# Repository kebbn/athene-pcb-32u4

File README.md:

# athene-pcb-32u4
 65% PCB design for the Athene keyboard by KL using the ATmega32u4 MCU.
 
 This project has been deprecated and is no longer supported. The more current design and variant is built off of the STM32F072 MCU, within the athene-pcb-f072 project.

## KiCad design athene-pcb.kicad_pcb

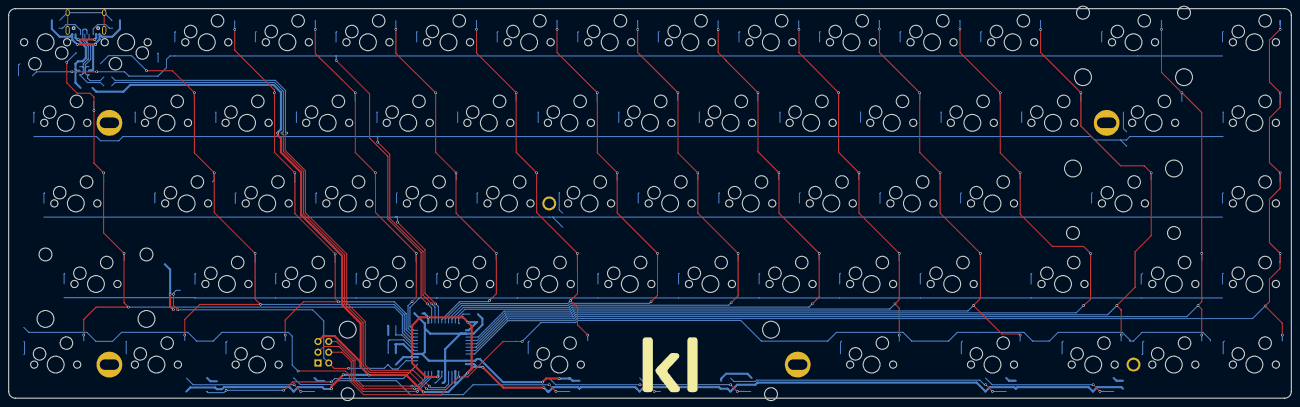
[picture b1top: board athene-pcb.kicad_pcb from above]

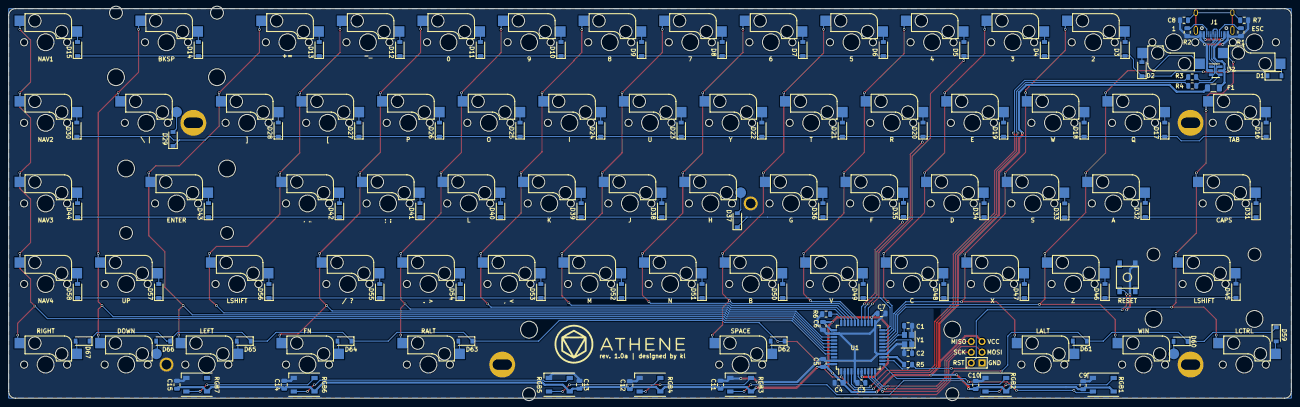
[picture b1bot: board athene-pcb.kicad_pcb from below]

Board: 2 copper layers, 303.2 x 92.1 mm, 182 parts (172 on the bottom side), 112 nets.

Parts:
C1, C2: 22pF; C_0805_2012Metric
C3: 1uF; C_0805_2012Metric
C4, C5, C6, C9, C10, C11, C12, C13, C14, C15: 0.1uF; C_0805_2012Metric
C7: 10uF; C_0805_2012Metric
C8: 4.7nF; C_0805_2012Metric
D1, D2, D3, D4, D5, D6, D7, D8, D9, D10, D11, D12, D13, D14, D15, D16, D17, D18, D19, D20, D21, D22, D23, D24, D25, D26, D27, D28, D29, D30, D31, D32, D33, D34, D35, D36, D37, D38, D39, D40, D41, D42, D43, D44, D45, D46, D47, D48, D49, D50, D51, D52, D53, D54, D55, D56, D57, D58, D59, D60, D61, D62, D63, D64, D65, D66, D67: D; D_SOD-123
F1: 500mA; Fuse_1206_3216Metric
HOLE5, HOLE5#2: MountingHole_4mm; MountingHole_M2
J1: HRO-TYPE-C-31-M-12
J2: AVR-ISP-6; Reset_Pretty-Mask
K1, K2, K3, K4, K5, K6, K7, K8, K9, K10, K11, K12, K13, K14, K15, K16, K17, K18, K19, K20, K21, K22, K23, K24, K25, K26, K27, K28, K30, K31, K32, K33, K34, K35, K36, K38, K39, K40, K41, K42, K43, K44, K45, K46, K47, K48, K49, K50, K51, K52, K53, K54, K55, K56, K57, K58, K59, K61, K62, K63, K64, K65, K67: KEYSW; Kailh_MX_Socket (3D)
K29, K37, K60, K66: KEYSW; Kailh_MX_Socket (3D) 1_Circle
Poker_oval_hole: VAL**; Poker_oval_hole
Poker_oval_hole#2, Poker_oval_hole#3, Poker_oval_hole#4: VAL**; Poker_oval_hole
R1, R2: 5.1k; R_0805_2012Metric
R3, R4: 22; R_0805_2012Metric
R5, R6: 10k; R_0805_2012Metric
R7: 1M; R_0805_2012Metric
RGB1, RGB2, RGB3, RGB4, RGB5, RGB6, RGB7: SK6812; LED_SK6812_PLCC4_5.0x5.0mm_P3.2mm
S1: SW_Push; SKQG-1155865
ST_BKSP: Stabilizer; Mx_Stab_200
ST_ENTER: Stabilizer; Mx_Stab_225
ST_LSHIFT: Stabilizer; Mx_Stab_200
ST_SPACE: Stabilizer; Mx_Stab_625
U1: ATmega32U4-AU; TQFP-44_10x10mm_P0.8mm
U2: SRV05-4-P-T7; SOT-23-6
Y1: XTAL; Crystal_SMD_3225-4Pin_3.2x2.5mm
athene logo: LOGO; athene
kl logo: LOGO; kl

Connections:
COL0: K1.1, K16.2, K31.2, K45.2, K59.2, U1.18 (PD0)
COL1: K2.2, K17.2, K32.2, K46.2, K60.2, U1.19 (PD1)
COL2: K3.2, K18.2, K33.2, K47.2, K61.2, U1.20 (PD2)
COL3: K4.2, K19.2, K34.2, K48.2, U1.21 (PD3)
COL4: K5.2, K20.2, K35.2, K49.2, U1.28 (PB4)
COL5: K6.2, K21.2, K36.2, K50.2, K62.2, U1.29 (PB5)
COL6: K7.2, K22.2, K37.2, K51.2, U1.30 (PB6)
COL7: K8.2, K23.2, K38.2, K52.2, U1.31 (PC6)
COL8: K9.2, K24.2, K39.2, K53.2, U1.32 (PC7)
COL9: K10.2, K25.2, K40.2, K54.2, K63.2, U1.36 (PF7)
COL10: K11.2, K26.2, K41.2, K55.2, K64.2, U1.37 (PF6)
COL11: K12.2, K27.2, K42.2, K56.2, U1.38 (PF5)
COL12: K13.2, K28.2, K43.2, K65.2, U1.39 (PF4)
COL13: K14.2, K29.2, K57.2, K66.2, U1.40 (PF1)
COL14: K15.2, K30.2, K44.2, K58.2, K67.2, U1.41 (PF0)
D+: R3.2, U1.4 (D+)
D-: R4.2, U1.3 (D-)
DBUS+: J1.6 (DP1), J1.8 (DP2), R3.1, U2.1 (IO1), U2.3 (IO2)
DBUS-: J1.5 (DN2), J1.7 (DN1), R4.1, U2.4 (IO3), U2.6 (IO4)
GND: C1.1, C2.1, C3.1, C4.2, C5.2, C6.2, C7.2, C8.2, C9.2, C10.2, C11.2, C12.2, C13.2, C14.2, C15.2, J1.1 (GND), J1.12 (GND), J2.6 (GND), R1.2, R2.2, R6.1, R7.1, RGB1.1 (VSS), RGB2.1 (VSS), RGB3.1 (VSS), RGB4.1 (VSS), RGB5.1 (VSS), RGB6.1 (VSS), RGB7.1 (VSS), S1.1, U1.5 (UGND), U1.15 (GND), U1.23 (GND), U1.35 (GND), U1.43 (GND), U2.2 (VN), Y1.2, Y1.4
MISO: J2.1 (MISO), U1.11 (PB3)
MOSI: J2.4 (MOSI), U1.10 (PB2)
unnamed: C1.2, U1.17 (XTAL1), Y1.3
unnamed: C2.2, U1.16 (XTAL2), Y1.1
unnamed: C3.2, U1.6 (UCAP)
unnamed: C8.1, J1.13 (SHIELD), R7.2
unnamed: D1.2 (A), K1.2
unnamed: D2.2 (A), K2.1
unnamed: D3.2 (A), K3.1
unnamed: D4.2 (A), K4.1
unnamed: D5.2 (A), K5.1
unnamed: D6.2 (A), K6.1
unnamed: D7.2 (A), K7.1
unnamed: D8.2 (A), K8.1
unnamed: D9.2 (A), K9.1
unnamed: D10.2 (A), K10.1
unnamed: D11.2 (A), K11.1
unnamed: D12.2 (A), K12.1
unnamed: D13.2 (A), K13.1
unnamed: D14.2 (A), K14.1
unnamed: D15.2 (A), K15.1
unnamed: D16.2 (A), K16.1
unnamed: D17.2 (A), K17.1
unnamed: D18.2 (A), K18.1
unnamed: D19.2 (A), K19.1
unnamed: D20.2 (A), K20.1
unnamed: D21.2 (A), K21.1
unnamed: D22.2 (A), K22.1
unnamed: D23.2 (A), K23.1
unnamed: D24.2 (A), K24.1
unnamed: D25.2 (A), K25.1
unnamed: D26.2 (A), K26.1
unnamed: D27.2 (A), K27.1
unnamed: D28.2 (A), K28.1
unnamed: D29.2 (A), K29.1
unnamed: D30.2 (A), K30.1
unnamed: D31.2 (A), K31.1
unnamed: D32.2 (A), K32.1
unnamed: D33.2 (A), K33.1
unnamed: D34.2 (A), K34.1
unnamed: D35.2 (A), K35.1
unnamed: D36.2 (A), K36.1
unnamed: D37.2 (A), K37.1
unnamed: D38.2 (A), K38.1
unnamed: D39.2 (A), K39.1
unnamed: D40.2 (A), K40.1
unnamed: D41.2 (A), K41.1
unnamed: D42.2 (A), K42.1
unnamed: D43.2 (A), K43.1
unnamed: D44.2 (A), K44.1
unnamed: D45.2 (A), K45.1
unnamed: D46.2 (A), K46.1
unnamed: D47.2 (A), K47.1
unnamed: D48.2 (A), K48.1
unnamed: D49.2 (A), K49.1
unnamed: D50.2 (A), K50.1
unnamed: D51.2 (A), K51.1
unnamed: D52.2 (A), K52.1
unnamed: D53.2 (A), K53.1
unnamed: D54.2 (A), K54.1
unnamed: D55.2 (A), K55.1
unnamed: D56.2 (A), K56.1
unnamed: D57.2 (A), K57.1
unnamed: D58.2 (A), K58.1
unnamed: D59.2 (A), K59.1
unnamed: D60.2 (A), K60.1
unnamed: D61.2 (A), K61.1
unnamed: D62.2 (A), K62.1
unnamed: D63.2 (A), K63.1
unnamed: D64.2 (A), K64.1
unnamed: D65.2 (A), K65.1
unnamed: D66.2 (A), K66.1
unnamed: D67.2 (A), K67.1
unnamed: J1.4 (CC1), R1.1
unnamed: J1.10 (CC2), R2.1
unnamed: R6.2, U1.33 (~HWB~/PE2)
unnamed: RGB1.4 (DOUT), RGB2.2 (DIN)
unnamed: RGB2.4 (DOUT), RGB3.2 (DIN)
unnamed: RGB3.4 (DOUT), RGB4.2 (DIN)
unnamed: RGB4.4 (DOUT), RGB5.2 (DIN)
unnamed: RGB5.4 (DOUT), RGB6.2 (DIN)
unnamed: RGB6.4 (DOUT), RGB7.2 (DIN)
RGB: RGB1.2 (DIN), U1.12 (PB7)
ROW0: D1.1 (K), D2.1 (K), D3.1 (K), D4.1 (K), D5.1 (K), D6.1 (K), D7.1 (K), D8.1 (K), D9.1 (K), D10.1 (K), D11.1 (K), D12.1 (K), D13.1 (K), D14.1 (K), D15.1 (K), U1.25 (PD4)
ROW1: D16.1 (K), D17.1 (K), D18.1 (K), D19.1 (K), D20.1 (K), D21.1 (K), D22.1 (K), D23.1 (K), D24.1 (K), D25.1 (K), D26.1 (K), D27.1 (K), D28.1 (K), D29.1 (K), D30.1 (K), U1.26 (PD6)
ROW2: D31.1 (K), D32.1 (K), D33.1 (K), D34.1 (K), D35.1 (K), D36.1 (K), D37.1 (K), D38.1 (K), D39.1 (K), D40.1 (K), D41.1 (K), D42.1 (K), D43.1 (K), D44.1 (K), U1.27 (PD7)
ROW3: D45.1 (K), D46.1 (K), D47.1 (K), D48.1 (K), D49.1 (K), D50.1 (K), D51.1 (K), D52.1 (K), D53.1 (K), D54.1 (K), D55.1 (K), D56.1 (K), D57.1 (K), D58.1 (K), U1.22 (PD5)
ROW4: D59.1 (K), D60.1 (K), D61.1 (K), D62.1 (K), D63.1 (K), D64.1 (K), D65.1 (K), D66.1 (K), D67.1 (K), U1.1 (PE6)
RST: J2.5 (~RST), R5.2, S1.2, U1.13 (~RESET)
SCLK: J2.3 (SCK), U1.9 (PB1)
VBUS: F1.1, J1.2 (VBUS), J1.11 (VBUS), U2.5 (VP)
VCC: C4.1, C5.1, C6.1, C7.1, C9.1, C10.1, C11.1, C12.1, C13.1, C14.1, C15.1, F1.2, J2.2 (VCC), R5.1, RGB1.3 (VDD), RGB2.3 (VDD), RGB3.3 (VDD), RGB4.3 (VDD), RGB5.3 (VDD), RGB6.3 (VDD), RGB7.3 (VDD), U1.2 (UVCC), U1.7 (VBUS), U1.14 (VCC), U1.24 (AVCC), U1.34 (VCC), U1.44 (AVCC)

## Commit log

2020-08-14 Project Initiate
2020-08-14 add submodules
2020-08-14 footprint libraries added
2020-08-14 Update fp-info-cache
2020-08-18 design updates
2020-08-19 v1 ready for review
2020-08-27 v1.0a update
2024-03-12 File cleanup
